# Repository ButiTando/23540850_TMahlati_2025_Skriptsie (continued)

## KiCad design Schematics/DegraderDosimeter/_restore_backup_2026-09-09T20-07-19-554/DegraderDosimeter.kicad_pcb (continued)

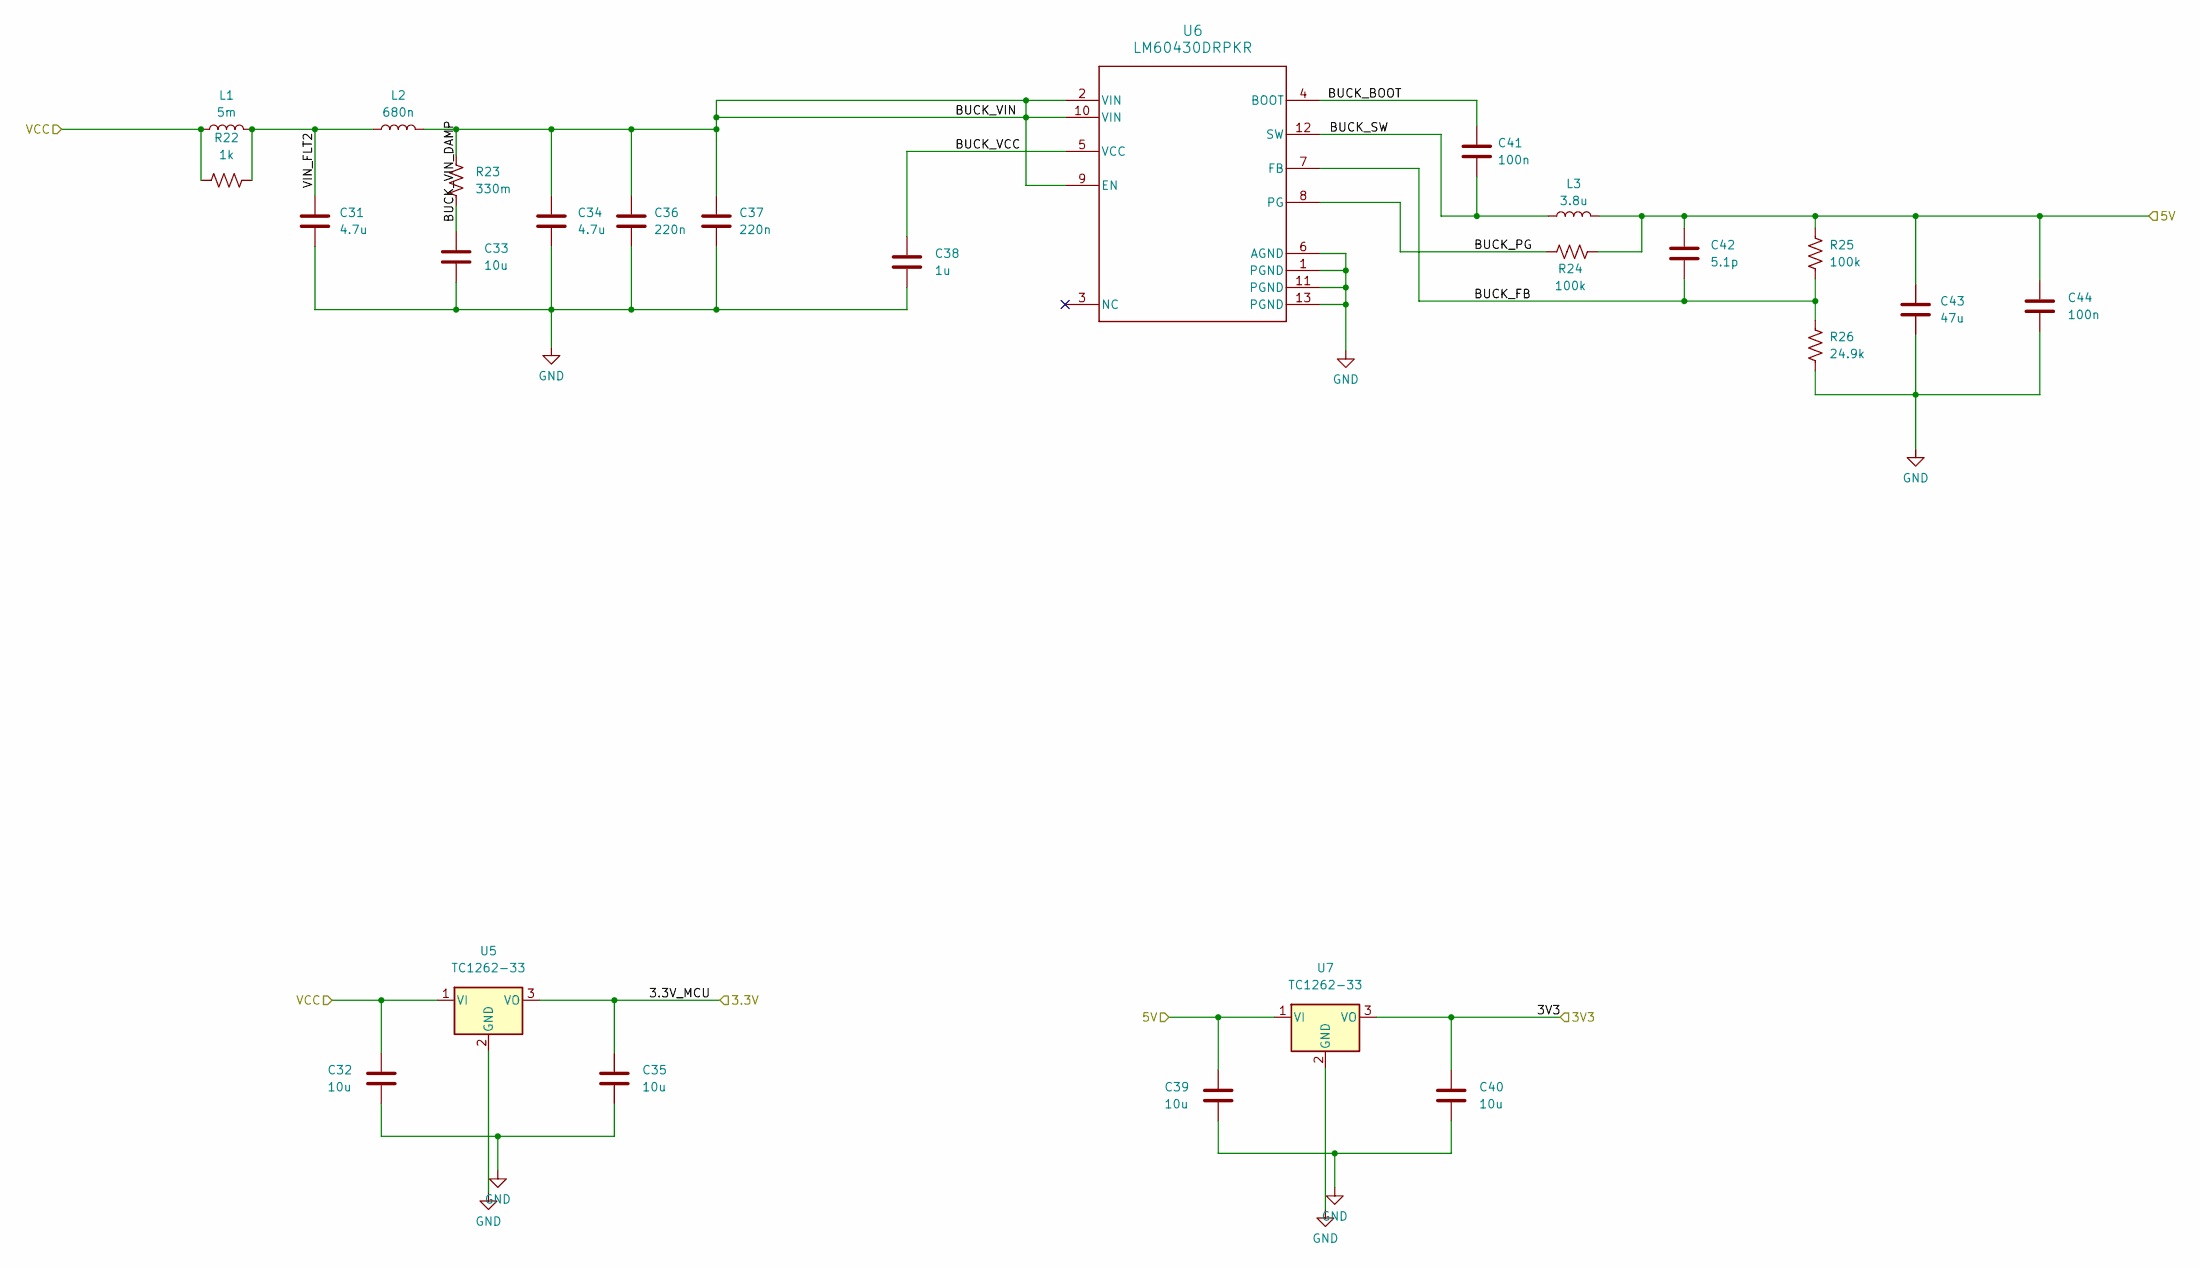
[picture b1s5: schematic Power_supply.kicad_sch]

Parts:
C31, C34: 4.7u; C_1206_3216Metric; LCSC C29823
C32: 10u; C_0805_2012Metric; LCSC C440198
C33, C35, C39, C40: 10u; C_0603_1608Metric; LCSC C19702
C36, C37: 220n; C_0805_2012Metric; LCSC C5378
C38: 1u; C_0603_1608Metric; LCSC C15849
C41, C44: 100n; C_0603_1608Metric; LCSC C14663
C42: 5.1p; C_0603_1608Metric
C43: 47u; C_1206_3216Metric; LCSC C96123
L1: 5m; L_Neosid_SM-PIC0512H
L2: 680n; L_Neosid_SM-PIC0512H
L3: 3.8u; L_1206_3216Metric_Pad1.22x1.90mm_HandSolder
R22: 1k; R_0603_1608Metric; LCSC C21190
R23: 330m; R_1206_3216Metric_Pad1.30x1.75mm_HandSolder
R24, R25: 100k; R_0603_1608Metric; LCSC C25803
R26: 24.9k; R_0603_1608Metric
U5, U7: TC1262-33; SOT-223-3
U6: LM60430DRPKR; RPK0013A-MFG

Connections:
/Power supply/3.3V_MCU: C35.1, U5.3 (VO)
/Power supply/3V3: C40.1, U7.3 (VO)
/Power supply/5V: C39.1, C42.1, C43.1, C44.1, L3.2, R24.1, R25.2, U7.1 (VI)
/Power supply/BUCK_BOOT: C41.1, U6.4 (BOOT)
/Power supply/BUCK_FB: C42.2, R25.1, R26.2, U6.7 (FB)
/Power supply/BUCK_PG: R24.2, U6.8 (PG)
/Power supply/BUCK_SW: C41.2, L3.1, U6.12 (SW)
/Power supply/BUCK_VCC: C38.1, U6.5 (VCC)
/Power supply/BUCK_VIN: C34.1, C36.1, C37.1, L2.2, R23.1, U6.2 (VIN), U6.9 (EN), U6.10 (VIN)
/Power supply/BUCK_VIN_DAMP: C33.1, R23.2
/Power supply/VCC: C32.1, L1.1, R22.1, U5.1 (VI)
/Power supply/VIN_FLT2: C31.1, L1.2, L2.1, R22.2
GND: C31.2, C32.2, C33.2, C34.2, C35.2, C36.2, C37.2, C38.2, C39.2, C40.2, C43.2, C44.2, R26.1, U5.2 (GND), U6.1 (PGND), U6.6 (AGND), U6.11 (PGND), U6.13 (PGND), U7.2 (GND); also elsewhere on the board

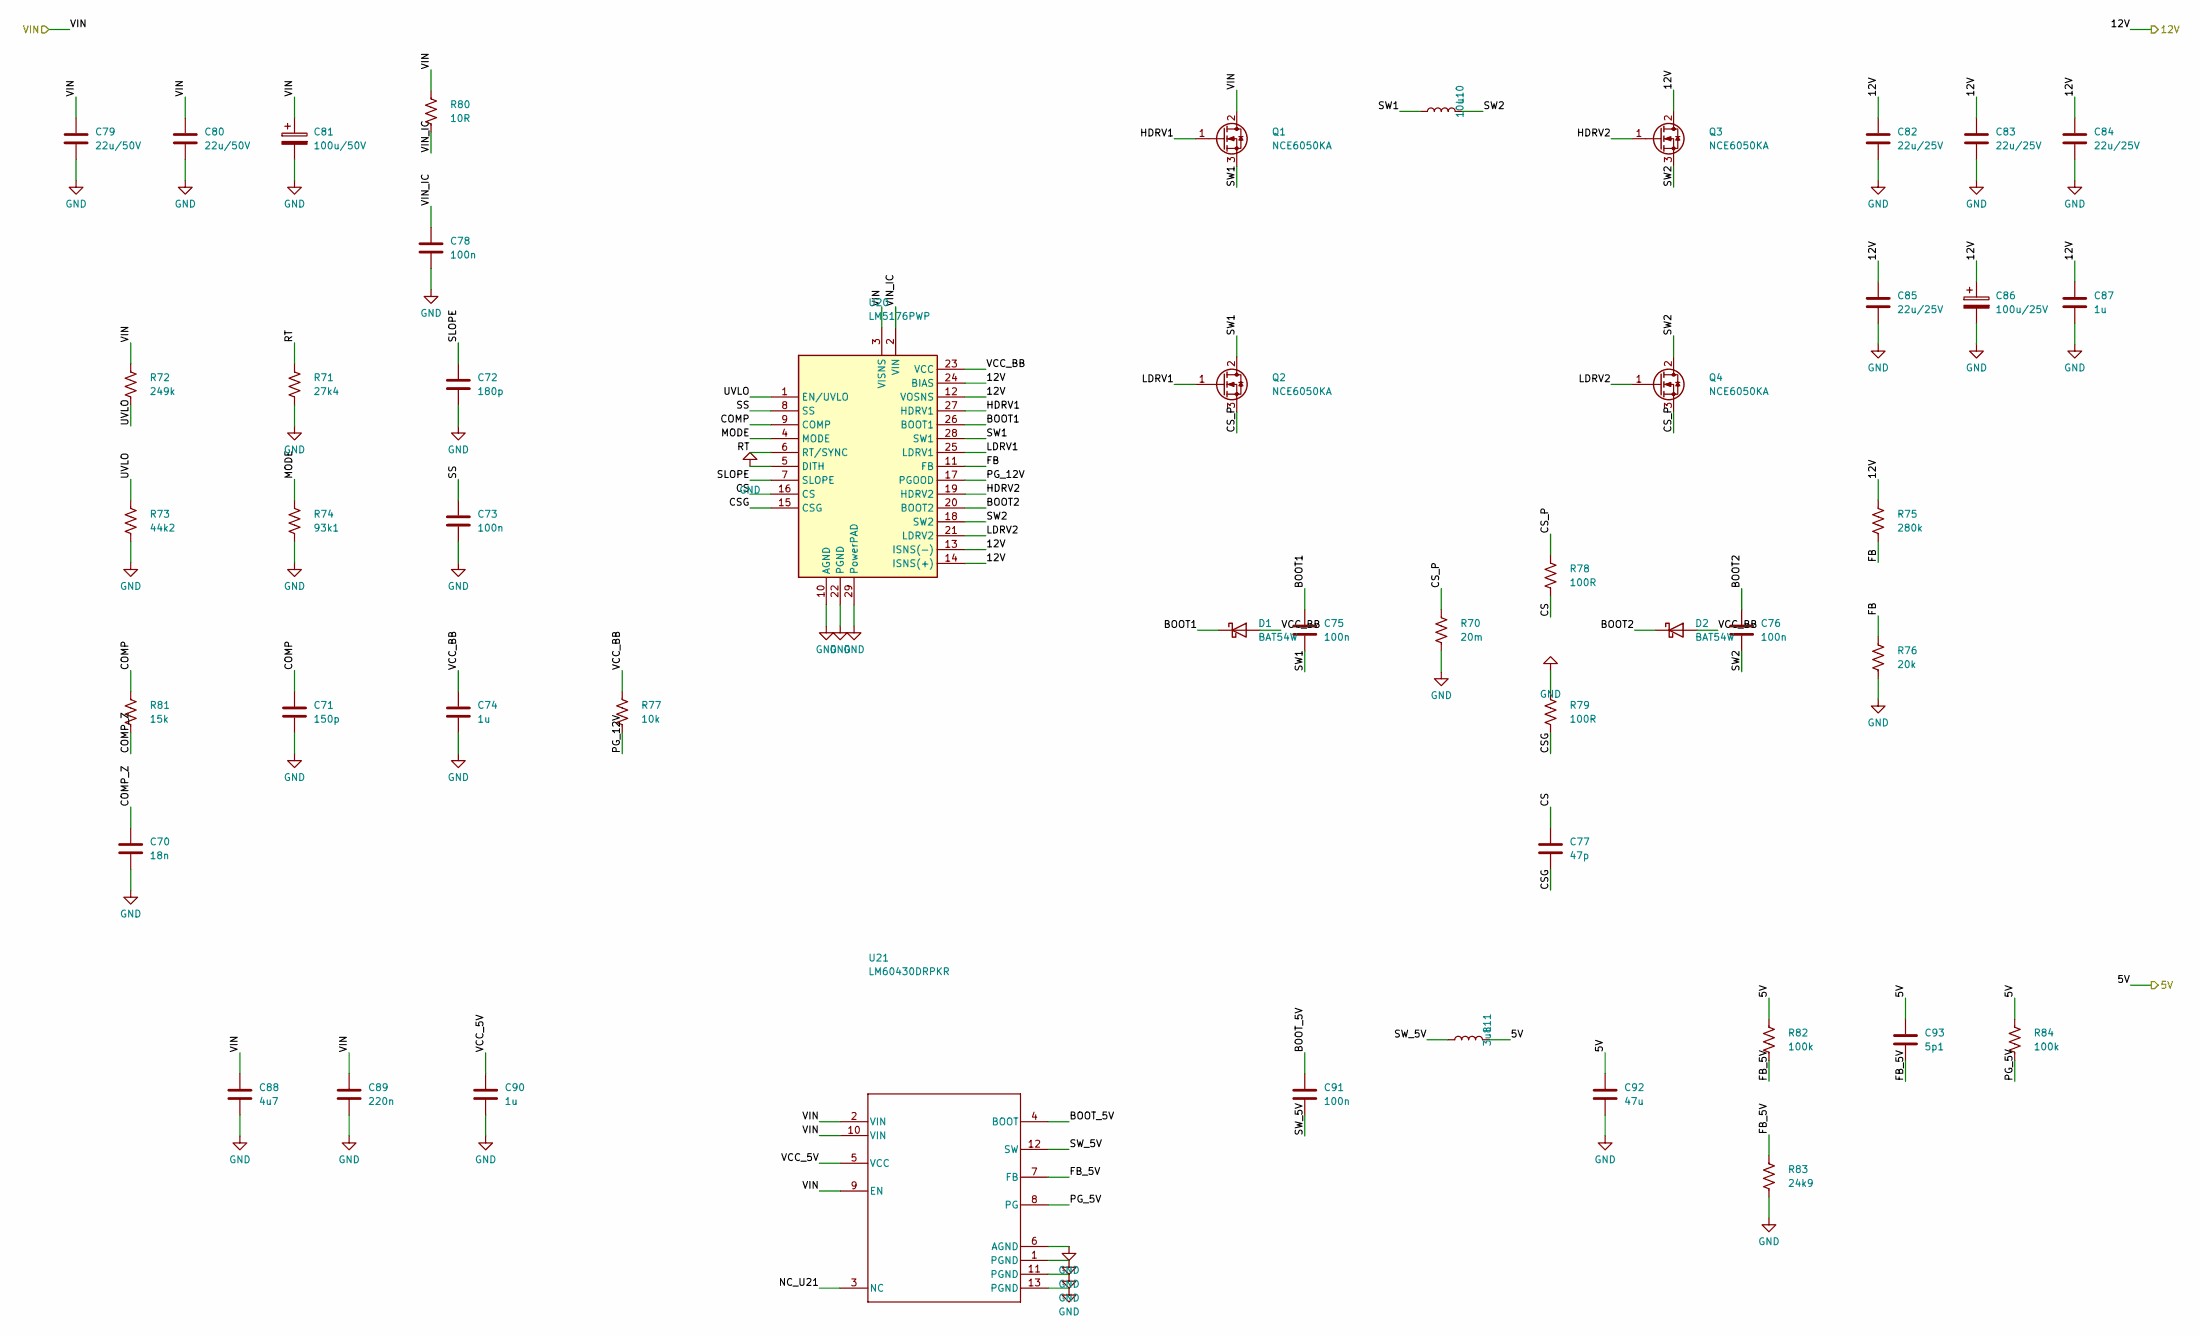
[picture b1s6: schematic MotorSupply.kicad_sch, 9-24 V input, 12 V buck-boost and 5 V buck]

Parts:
C70: 18n; C_0603_1608Metric
C71: 150p; C_0603_1608Metric; LCSC C1594
C72: 180p; C_0603_1608Metric
C73, C75, C76, C78, C91: 100n; C_0603_1608Metric; LCSC C14663
C74, C87, C90: 1u; C_0603_1608Metric; LCSC C15849
C77: 47p; C_0603_1608Metric; LCSC C1671
C79, C80: 22u/50V; C_1210_3225Metric
C81: 100u/50V; CP_Elec_8x10.5
C82, C83, C84, C85: 22u/25V; C_0805_2012Metric; LCSC C45783
C86: 100u/25V; CP_Elec_6.3x7.7
C88: 4u7; C_1206_3216Metric; LCSC C29823
C89: 220n; C_0805_2012Metric; LCSC C5378
C92: 47u; C_1206_3216Metric; LCSC C96123
C93: 5p1; C_0603_1608Metric
D1, D2: BAT54W; D_SOD-323; LCSC C32180
L10: 10u; L_12x12mm_H8mm; LCSC C19268657
L11: 3u8; L_7.3x7.3_H4.5
Q1, Q2, Q3, Q4: NCE6050KA; TO-252-3_TabPin2; LCSC C96013
R70: 20m; R_2512_6332Metric
R71: 27k4; R_0603_1608Metric
R72: 249k; R_0603_1608Metric
R73: 44k2; R_0603_1608Metric
R74: 93k1; R_0603_1608Metric
R75: 280k; R_0603_1608Metric
R76: 20k; R_0603_1608Metric; LCSC C4184
R77: 10k; R_0603_1608Metric; LCSC C25804
R78, R79: 100R; R_0603_1608Metric; LCSC C22775
R80: 10R; R_0603_1608Metric; LCSC C22859
R81: 15k; R_0603_1608Metric; LCSC C22809
R82, R84: 100k; R_0603_1608Metric; LCSC C25803
R83: 24k9; R_0603_1608Metric
U20: LM5176PWP; HTSSOP-28-1EP_4.4x9.7mm_P0.65mm_EP3.4x9.5mm_ThermalVias; LCSC C442493
U21: LM60430DRPKR; RPK0013A-MFG; LCSC C2873217

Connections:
/MotorSupply/5V: C92.1, C93.1, L11.2, R82.1, R84.1
/MotorSupply/12V: C82.1, C83.1, C84.1, C85.1, C86.1, C87.1, Q3.2 (D), R75.1, U20.12 (VOSNS), U20.13 (ISNS(-)), U20.14 (ISNS(+)), U20.24 (BIAS)
/MotorSupply/BOOT1: C75.1, D1.1 (K), U20.26 (BOOT1)
/MotorSupply/BOOT2: C76.1, D2.1 (K), U20.20 (BOOT2)
/MotorSupply/BOOT_5V: C91.1, U21.4 (BOOT)
/MotorSupply/COMP: C71.1, R81.1, U20.9 (COMP)
/MotorSupply/COMP_Z: C70.1, R81.2
/MotorSupply/CS: C77.1, R78.2, U20.16 (CS)
/MotorSupply/CSG: C77.2, R79.2, U20.15 (CSG)
/MotorSupply/CS_P: Q2.3 (S), Q4.3 (S), R70.1, R78.1
/MotorSupply/FB: R75.2, R76.1, U20.11 (FB)
/MotorSupply/FB_5V: C93.2, R82.2, R83.1, U21.7 (FB)
/MotorSupply/HDRV1: Q1.1 (G), U20.27 (HDRV1)
/MotorSupply/HDRV2: Q3.1 (G), U20.19 (HDRV2)
/MotorSupply/LDRV1: Q2.1 (G), U20.25 (LDRV1)
/MotorSupply/LDRV2: Q4.1 (G), U20.21 (LDRV2)
/MotorSupply/MODE: R74.1, U20.4 (MODE)
/MotorSupply/NC_U21: U21.3 (NC)
/MotorSupply/PG_5V: R84.2, U21.8 (PG)
/MotorSupply/PG_12V: R77.2, U20.17 (PGOOD)
/MotorSupply/RT: R71.1, U20.6 (RT/SYNC)
/MotorSupply/SLOPE: C72.1, U20.7 (SLOPE)
/MotorSupply/SS: C73.1, U20.8 (SS)
/MotorSupply/SW1: C75.2, L10.1, Q1.3 (S), Q2.2 (D), U20.28 (SW1)
/MotorSupply/SW2: C76.2, L10.2, Q3.3 (S), Q4.2 (D), U20.18 (SW2)
/MotorSupply/SW_5V: C91.2, L11.1, U21.12 (SW)
/MotorSupply/UVLO: R72.2, R73.1, U20.1 (EN/UVLO)
/MotorSupply/VCC_5V: C90.1, U21.5 (VCC)
/MotorSupply/VCC_BB: C74.1, D1.2 (A), D2.2 (A), R77.1, U20.23 (VCC)
/MotorSupply/VIN: C79.1, C80.1, C81.1, C88.1, C89.1, Q1.2 (D), R72.1, R80.1, U20.3 (VISNS), U21.2 (VIN), U21.9 (EN), U21.10 (VIN)
/MotorSupply/VIN_IC: C78.1, R80.2, U20.2 (VIN)
GND: C70.2, C71.2, C72.2, C73.2, C74.2, C78.2, C79.2, C80.2, C81.2, C82.2, C83.2, C84.2, C85.2, C86.2, C87.2, C88.2, C89.2, C90.2, C92.2, R70.2, R71.2, R73.2, R74.2, R76.2, R79.1, R83.2, U20.5 (DITH), U20.10 (AGND), U20.22 (PGND), U20.29 (PowerPAD), U21.1 (PGND), U21.6 (AGND), U21.11 (PGND), U21.13 (PGND); also elsewhere on the board

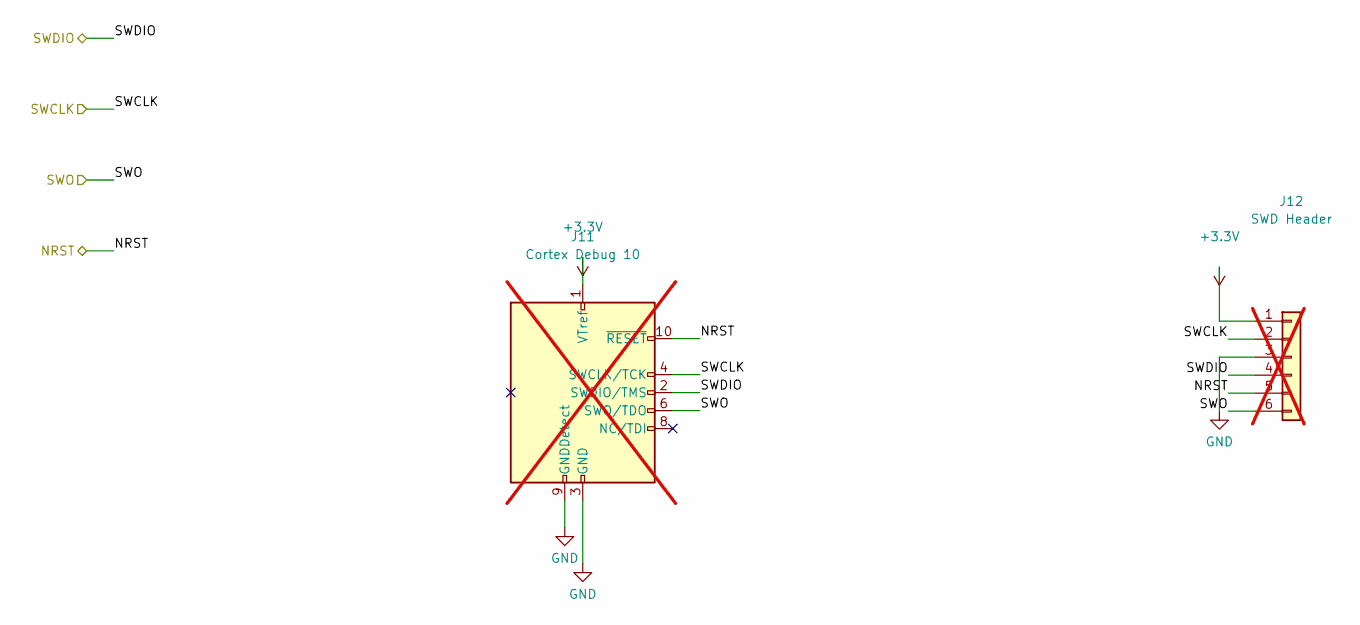
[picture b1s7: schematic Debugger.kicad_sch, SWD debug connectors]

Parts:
J11: Cortex Debug 10; PinHeader_2x05_P1.27mm_Vertical; not fitted
J12: SWD Header; PinHeader_1x06_P2.54mm_Vertical; not fitted

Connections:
+3.3V: J11.1 (VTref), J12.1; also elsewhere on the board
/Debugger/NRST: J11.10 (~RESET), J12.5
/Debugger/SWCLK: J11.4 (SWCLK/TCK), J12.2; also elsewhere on the board
/Debugger/SWDIO: J11.2 (SWDIO/TMS), J12.4; also elsewhere on the board
/Debugger/SWO: J11.6 (SWO/TDO), J12.6; also elsewhere on the board
GND: J11.3 (GND), J11.5 (GND), J11.9 (GNDDetect), J12.3; also elsewhere on the board

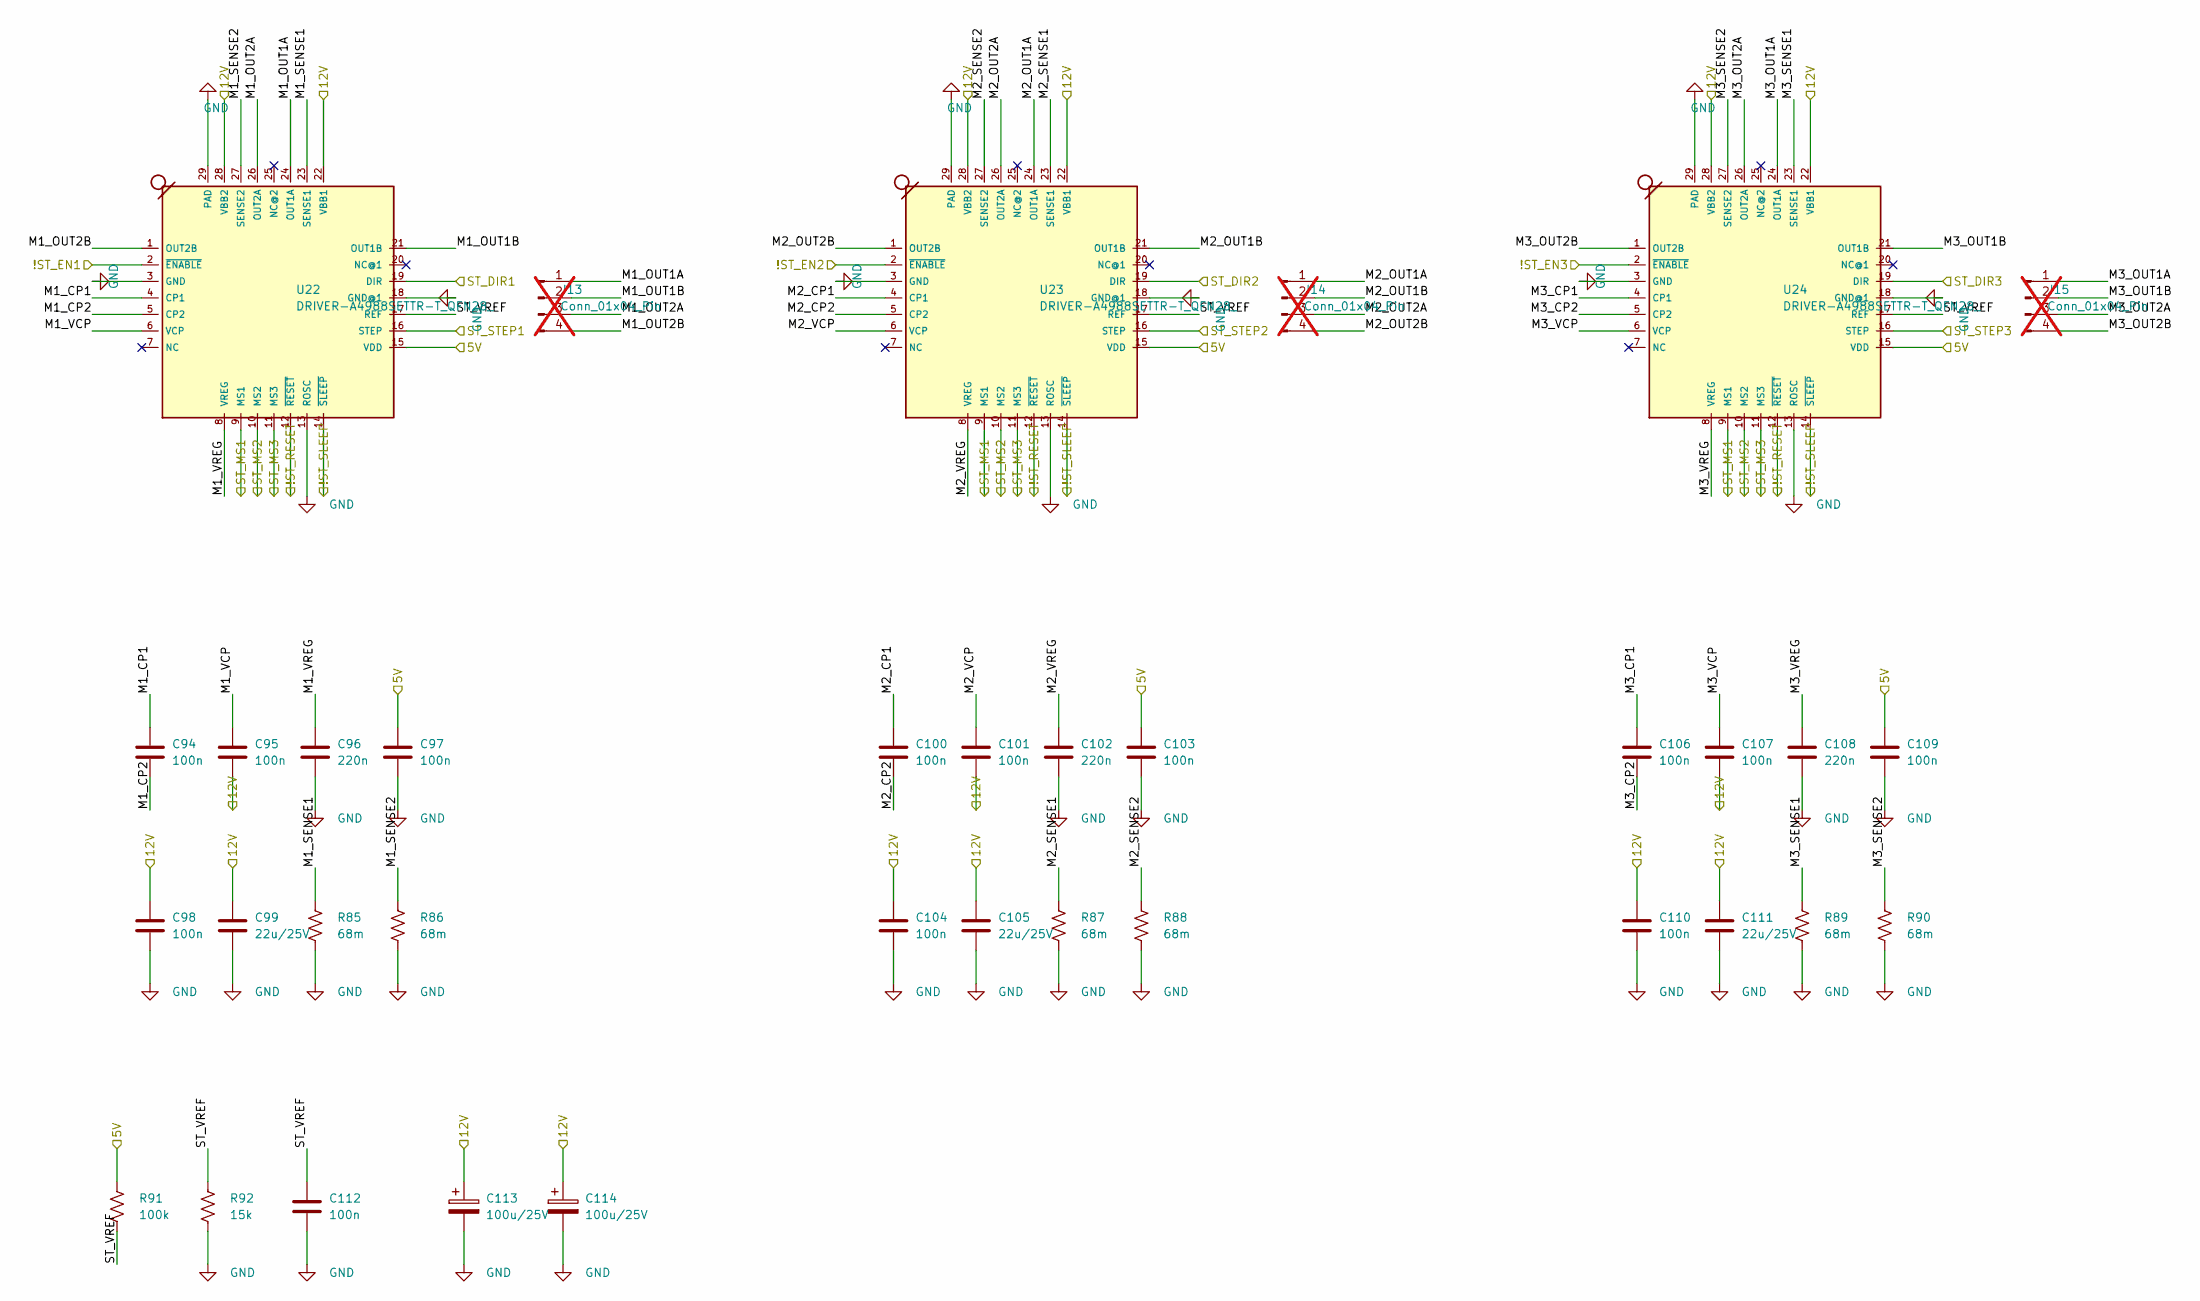
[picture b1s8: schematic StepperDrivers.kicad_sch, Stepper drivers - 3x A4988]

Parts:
C94, C95, C97, C98, C100, C101, C103, C104, C106, C107, C109, C110, C112: 100n; C_0603_1608Metric; LCSC C14663
C96, C102, C108: 220n; C_0805_2012Metric; LCSC C5378
C99, C105, C111: 22u/25V; C_0805_2012Metric; LCSC C45783
C113, C114: 100u/25V; CP_Elec_6.3x7.7
J13, J14, J15: Conn_01x04_Pin; SolderWire-2sqmm_1x04_P7.8mm_D2mm_OD3.9mm; not fitted
R85, R86, R87, R88, R89, R90: 68m; R_1206_3216Metric_Pad1.30x1.75mm_HandSolder
R91: 100k; R_0603_1608Metric; LCSC C25803
R92: 15k; R_0603_1608Metric; LCSC C22809
U22, U23, U24: DRIVER-A4988SETTR-T_QFN28_; QFN28G_0.5-5X5MM; MPN A4988SETTR-T

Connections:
/MCU_H723/!ST_EN1: U22.2 (~ENABLE); also elsewhere on the board
/MCU_H723/!ST_EN2: U23.2 (~ENABLE); also elsewhere on the board
/MCU_H723/!ST_EN3: U24.2 (~ENABLE); also elsewhere on the board
/MCU_H723/!ST_RESET: U22.12 (~RESET), U23.12 (~RESET), U24.12 (~RESET); also elsewhere on the board
/MCU_H723/!ST_SLEEP: U22.14 (~SLEEP), U23.14 (~SLEEP), U24.14 (~SLEEP); also elsewhere on the board
/MCU_H723/ST_DIR1: U22.19 (DIR); also elsewhere on the board
/MCU_H723/ST_DIR2: U23.19 (DIR); also elsewhere on the board
/MCU_H723/ST_DIR3: U24.19 (DIR); also elsewhere on the board
/MCU_H723/ST_MS1: U22.9 (MS1), U23.9 (MS1), U24.9 (MS1); also elsewhere on the board
/MCU_H723/ST_MS2: U22.10 (MS2), U23.10 (MS2), U24.10 (MS2); also elsewhere on the board
/MCU_H723/ST_MS3: U22.11 (MS3), U23.11 (MS3), U24.11 (MS3); also elsewhere on the board
/MCU_H723/ST_STEP1: U22.16 (STEP); also elsewhere on the board
/MCU_H723/ST_STEP2: U23.16 (STEP); also elsewhere on the board
/MCU_H723/ST_STEP3: U24.16 (STEP); also elsewhere on the board
/StepperDrivers/5V: C97.1, C103.1, C109.1, R91.1, U22.15 (VDD), U23.15 (VDD), U24.15 (VDD)
/StepperDrivers/12V: C95.2, C98.1, C99.1, C101.2, C104.1, C105.1, C107.2, C110.1, C111.1, C113.1, C114.1, U22.22 (VBB1), U22.28 (VBB2), U23.22 (VBB1), U23.28 (VBB2), U24.22 (VBB1), U24.28 (VBB2)
/StepperDrivers/M1_CP1: C94.1, U22.4 (CP1)
/StepperDrivers/M1_CP2: C94.2, U22.5 (CP2)
/StepperDrivers/M1_OUT1A: J13.1, U22.24 (OUT1A)
/StepperDrivers/M1_OUT1B: J13.2, U22.21 (OUT1B)
/StepperDrivers/M1_OUT2A: J13.3, U22.26 (OUT2A)
/StepperDrivers/M1_OUT2B: J13.4, U22.1 (OUT2B)
/StepperDrivers/M1_SENSE1: R85.1, U22.23 (SENSE1)
/StepperDrivers/M1_SENSE2: R86.1, U22.27 (SENSE2)
/StepperDrivers/M1_VCP: C95.1, U22.6 (VCP)
/StepperDrivers/M1_VREG: C96.1, U22.8 (VREG)
/StepperDrivers/M2_CP1: C100.1, U23.4 (CP1)
/StepperDrivers/M2_CP2: C100.2, U23.5 (CP2)
/StepperDrivers/M2_OUT1A: J14.1, U23.24 (OUT1A)
/StepperDrivers/M2_OUT1B: J14.2, U23.21 (OUT1B)
/StepperDrivers/M2_OUT2A: J14.3, U23.26 (OUT2A)
/StepperDrivers/M2_OUT2B: J14.4, U23.1 (OUT2B)
/StepperDrivers/M2_SENSE1: R87.1, U23.23 (SENSE1)
/StepperDrivers/M2_SENSE2: R88.1, U23.27 (SENSE2)
/StepperDrivers/M2_VCP: C101.1, U23.6 (VCP)
/StepperDrivers/M2_VREG: C102.1, U23.8 (VREG)
/StepperDrivers/M3_CP1: C106.1, U24.4 (CP1)
/StepperDrivers/M3_CP2: C106.2, U24.5 (CP2)
/StepperDrivers/M3_OUT1A: J15.1, U24.24 (OUT1A)
/StepperDrivers/M3_OUT1B: J15.2, U24.21 (OUT1B)
/StepperDrivers/M3_OUT2A: J15.3, U24.26 (OUT2A)
/StepperDrivers/M3_OUT2B: J15.4, U24.1 (OUT2B)
/StepperDrivers/M3_SENSE1: R89.1, U24.23 (SENSE1)
/StepperDrivers/M3_SENSE2: R90.1, U24.27 (SENSE2)
/StepperDrivers/M3_VCP: C107.1, U24.6 (VCP)
/StepperDrivers/M3_VREG: C108.1, U24.8 (VREG)
/StepperDrivers/ST_VREF: C112.1, R91.2, R92.1, U22.17 (REF), U23.17 (REF), U24.17 (REF)
GND: C96.2, C97.2, C98.2, C99.2, C102.2, C103.2, C104.2, C105.2, C108.2, C109.2, C110.2, C111.2, C112.2, C113.2, C114.2, R85.2, R86.2, R87.2, R88.2, R89.2, R90.2, R92.2, U22.3 (GND), U22.13 (ROSC), U22.18 (GND@1), U22.29 (PAD), U23.3 (GND), U23.13 (ROSC), U23.18 (GND@1), U23.29 (PAD), U24.3 (GND), U24.13 (ROSC), U24.18 (GND@1), U24.29 (PAD); also elsewhere on the board

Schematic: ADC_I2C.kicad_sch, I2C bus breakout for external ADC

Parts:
C115: 100n; C_0603_1608Metric; LCSC C14663
J16: Conn_01x06; PinHeader_1x06_P2.54mm_Vertical
R93, R94: 4k7; R_0603_1608Metric; LCSC C23162
R95: 10k; R_0603_1608Metric; LCSC C25804

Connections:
+3.3V: C115.1, J16.1, R93.1, R94.1, R95.1; also elsewhere on the board
/ADC_I2C/!ADC_ALERT: J16.5, R95.2; also elsewhere on the board
/ADC_I2C/I2C1_SCL: J16.3, R93.2; also elsewhere on the board
/ADC_I2C/I2C1_SDA: J16.4, R94.2; also elsewhere on the board
GND: C115.2, J16.2, J16.6; also elsewhere on the board

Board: 4 copper layers, 288 parts (0 on the bottom side), 233 nets, no tracks yet.

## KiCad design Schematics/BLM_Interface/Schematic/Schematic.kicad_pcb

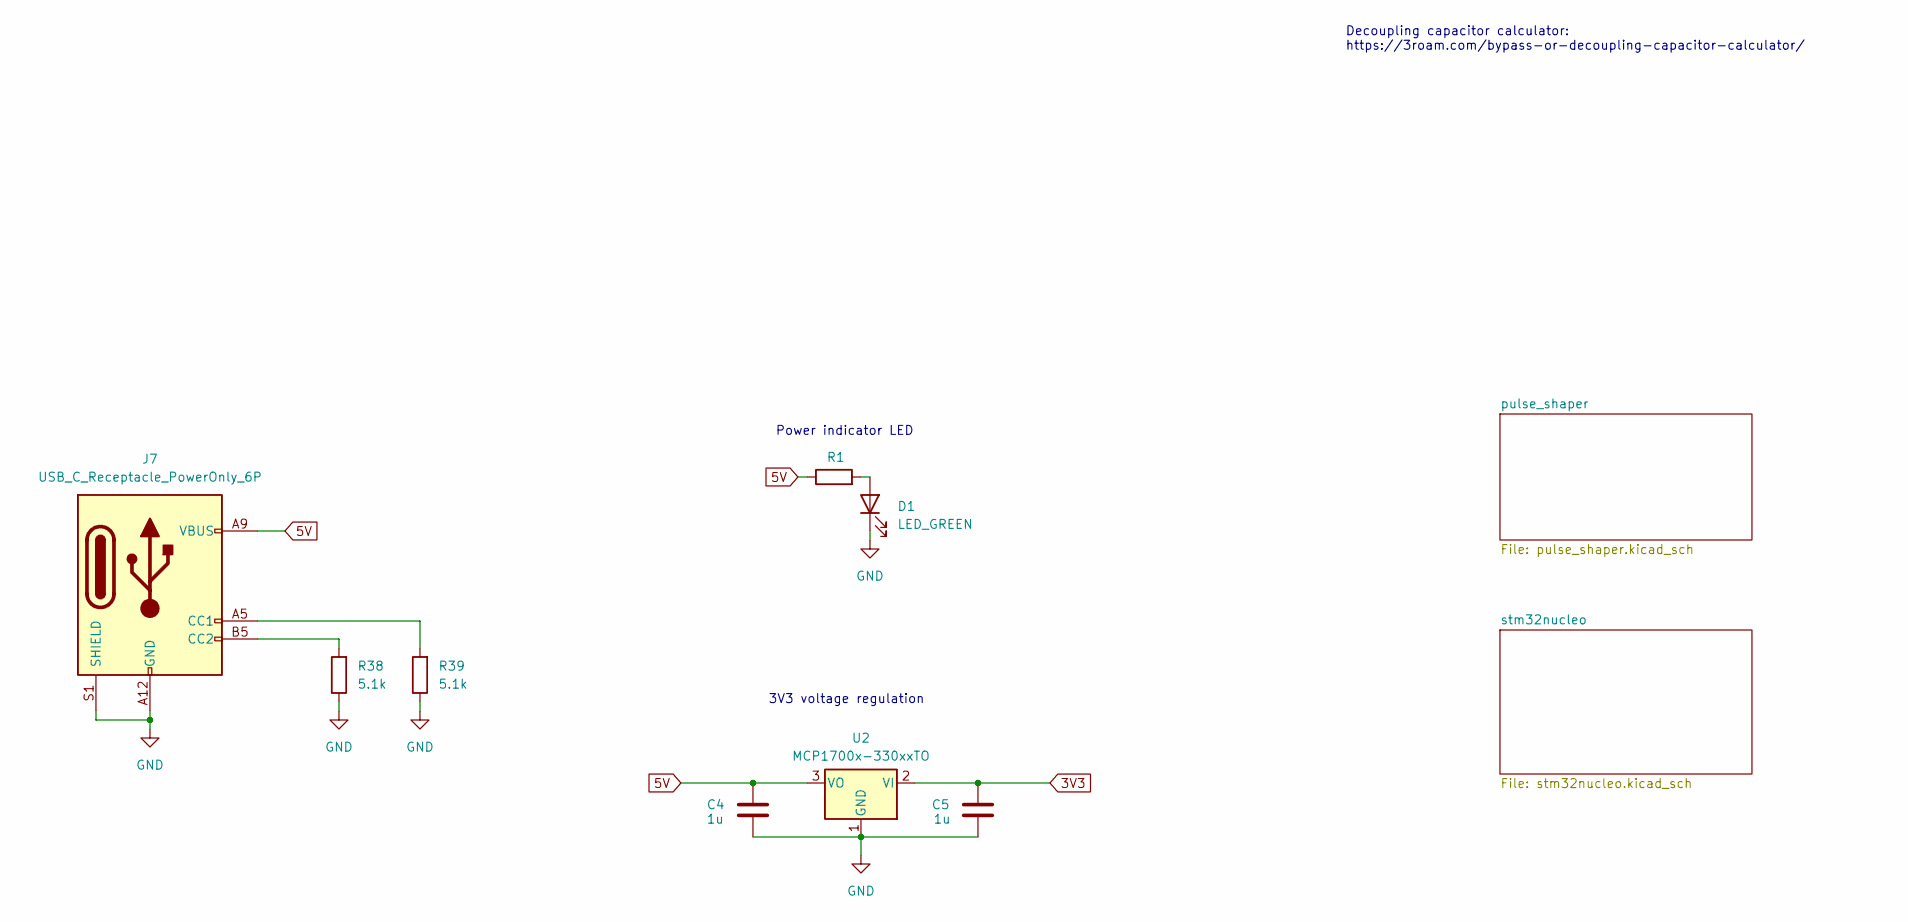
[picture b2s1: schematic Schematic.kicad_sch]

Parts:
C4, C5: 1u; C_Disc_D12.5mm_W5.0mm_P10.00mm
D1: LED_GREEN; LED_D3.0mm_Horizontal_O3.81mm_Z2.0mm
J7: USB_C_Receptacle_PowerOnly_6P; USB_C_Receptacle_GCT_USB4125-xx-x_6P_TopMnt_Horizontal
R1: 660; R_Axial_DIN0204_L3.6mm_D1.6mm_P5.08mm_Horizontal
R38, R39: 5.1k; R_2010_5025Metric_Pad1.40x2.65mm_HandSolder
U2: MCP1700x-330xxTO; TO-92_Inline_Wide

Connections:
3V3: C5.1, U2.2 (VI); also elsewhere on the board
5V: C4.1, J7.A9 (VBUS), J7.B9 (VBUS), R1.1, U2.3 (VO); also elsewhere on the board
GND: C4.2, C5.2, D1.1 (K), J7.A12 (GND), J7.B12 (GND), J7.S1 (SHIELD), R38.1, R39.1, U2.1 (GND); also elsewhere on the board
unnamed: D1.2 (A), R1.2
unnamed: J7.A5 (CC1), R39.2
unnamed: J7.B5 (CC2), R38.2

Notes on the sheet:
Decoupling capacitor calculator: https://3roam.com/bypass-or-decoupling-capacitor-calculator/
Power indicator LED
3V3 voltage regulation

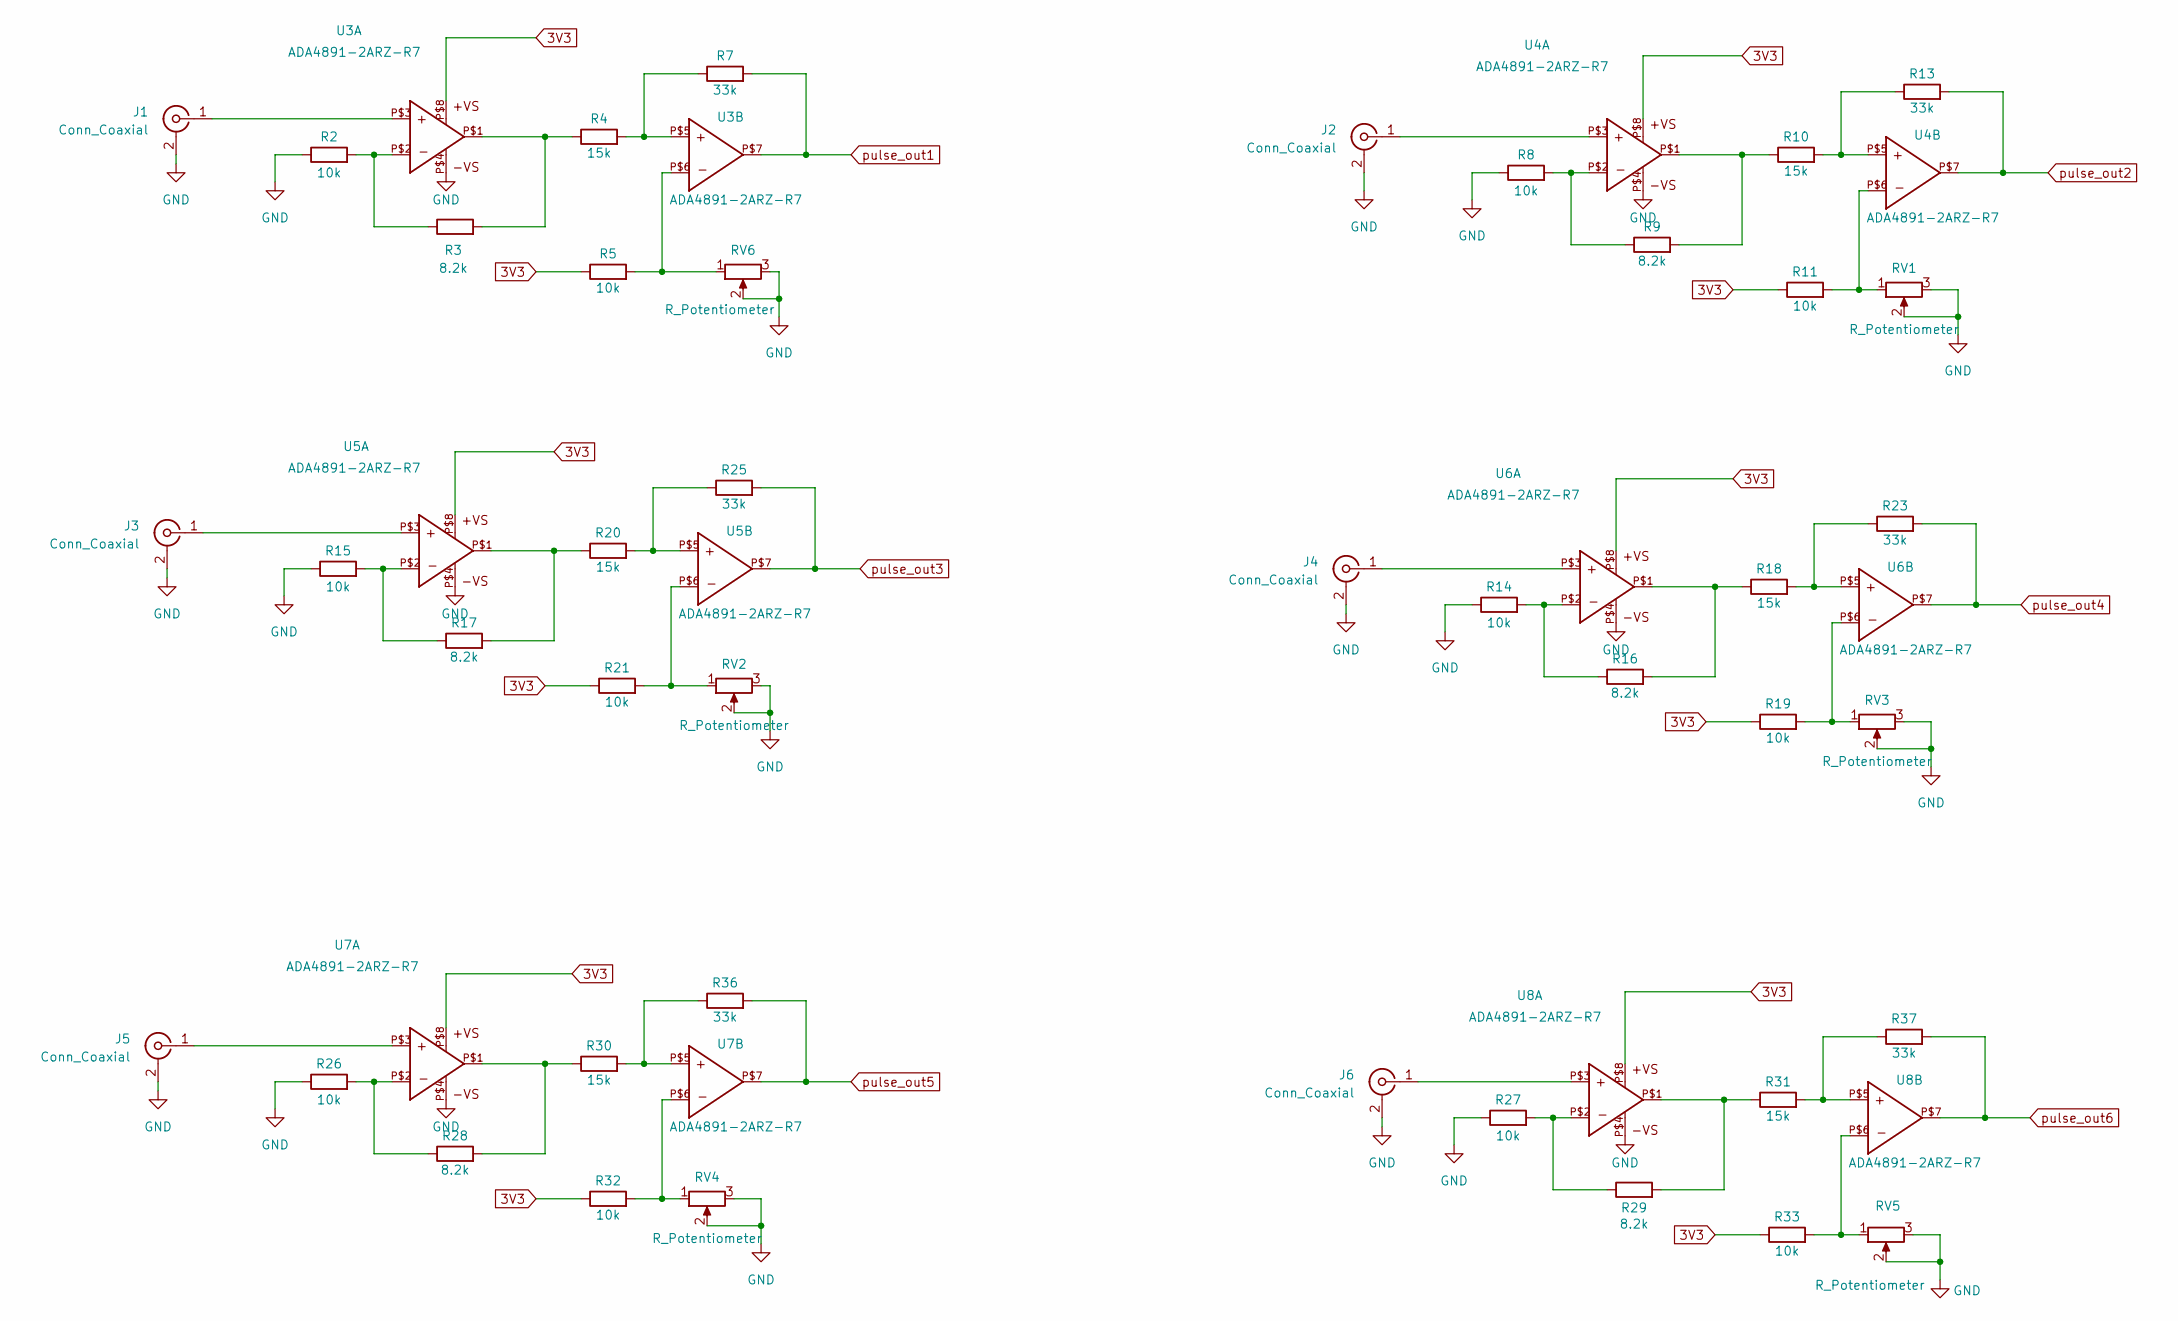
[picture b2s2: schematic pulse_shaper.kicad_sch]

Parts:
J1, J2, J3, J4, J5, J6: Conn_Coaxial; BNC_Amphenol_B6252HB-NPP3G-50_Horizontal
R2, R5, R8, R11, R14, R15, R19, R21, R26, R27, R32, R33: 10k; R_Axial_DIN0204_L3.6mm_D1.6mm_P5.08mm_Horizontal
R3, R9, R16, R17, R28, R29: 8.2k; R_Axial_DIN0204_L3.6mm_D1.6mm_P5.08mm_Horizontal
R4, R10, R18, R20, R30, R31: 15k; R_Axial_DIN0204_L3.6mm_D1.6mm_P5.08mm_Horizontal
R7, R13, R23, R25, R36, R37: 33k; R_Axial_DIN0204_L3.6mm_D1.6mm_P5.08mm_Horizontal
RV1, RV2, RV3, RV4, RV5, RV6: R_Potentiometer; Potentiometer_Bourns_3299Y_Vertical
U3, U4, U5, U6, U7, U8: ADA4891-2ARZ-R7; SOIC8; PARTNO ADA4891-2ARZ-R7CT-ND

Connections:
3V3: R5.1, R11.1, R19.1, R21.1, R32.1, R33.1, U3.P$8, U4.P$8, U5.P$8, U6.P$8, U7.P$8, U8.P$8; also elsewhere on the board
GND: J1.2 (Ext), J2.2 (Ext), J3.2 (Ext), J4.2 (Ext), J5.2 (Ext), J6.2 (Ext), R2.1, R8.1, R14.1, R15.1, R26.1, R27.1, RV1.2, RV1.3, RV2.2, RV2.3, RV3.2, RV3.3, RV4.2, RV4.3, RV5.2, RV5.3, RV6.2, RV6.3, U3.P$4, U4.P$4, U5.P$4, U6.P$4, U7.P$4, U8.P$4; also elsewhere on the board
unnamed: J1.1 (In), U3.P$3
unnamed: J2.1 (In), U4.P$3
unnamed: J3.1 (In), U5.P$3
unnamed: J4.1 (In), U6.P$3
unnamed: J5.1 (In), U7.P$3
unnamed: J6.1 (In), U8.P$3
unnamed: R2.2, R3.1, U3.P$2
unnamed: R3.2, R4.1, U3.P$1
unnamed: R4.2, R7.1, U3.P$5
unnamed: R5.2, RV6.1, U3.P$6
unnamed: R8.2, R9.1, U4.P$2
unnamed: R9.2, R10.1, U4.P$1
unnamed: R10.2, R13.1, U4.P$5
unnamed: R11.2, RV1.1, U4.P$6
unnamed: R14.2, R16.1, U6.P$2
unnamed: R15.2, R17.1, U5.P$2
unnamed: R16.2, R18.1, U6.P$1
unnamed: R17.2, R20.1, U5.P$1
unnamed: R18.2, R23.1, U6.P$5
unnamed: R19.2, RV3.1, U6.P$6
unnamed: R20.2, R25.1, U5.P$5
unnamed: R21.2, RV2.1, U5.P$6
unnamed: R26.2, R28.1, U7.P$2
unnamed: R27.2, R29.1, U8.P$2
unnamed: R28.2, R30.1, U7.P$1
unnamed: R29.2, R31.1, U8.P$1
unnamed: R30.2, R36.1, U7.P$5
unnamed: R31.2, R37.1, U8.P$5
unnamed: R32.2, RV4.1, U7.P$6
unnamed: R33.2, RV5.1, U8.P$6
pulse_out1: R7.2, U3.P$7; also elsewhere on the board
pulse_out2: R13.2, U4.P$7; also elsewhere on the board
pulse_out3: R25.2, U5.P$7; also elsewhere on the board
pulse_out4: R23.2, U6.P$7; also elsewhere on the board
pulse_out5: R36.2, U7.P$7; also elsewhere on the board
pulse_out6: R37.2, U8.P$7; also elsewhere on the board
